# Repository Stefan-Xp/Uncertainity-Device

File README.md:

# Uncertainity-Device
Uncertainity Device - A small PCB with ESP32s2 and WS2812 compatible LEDs

Attention: This Design is not yet tested, so proceed with caution!

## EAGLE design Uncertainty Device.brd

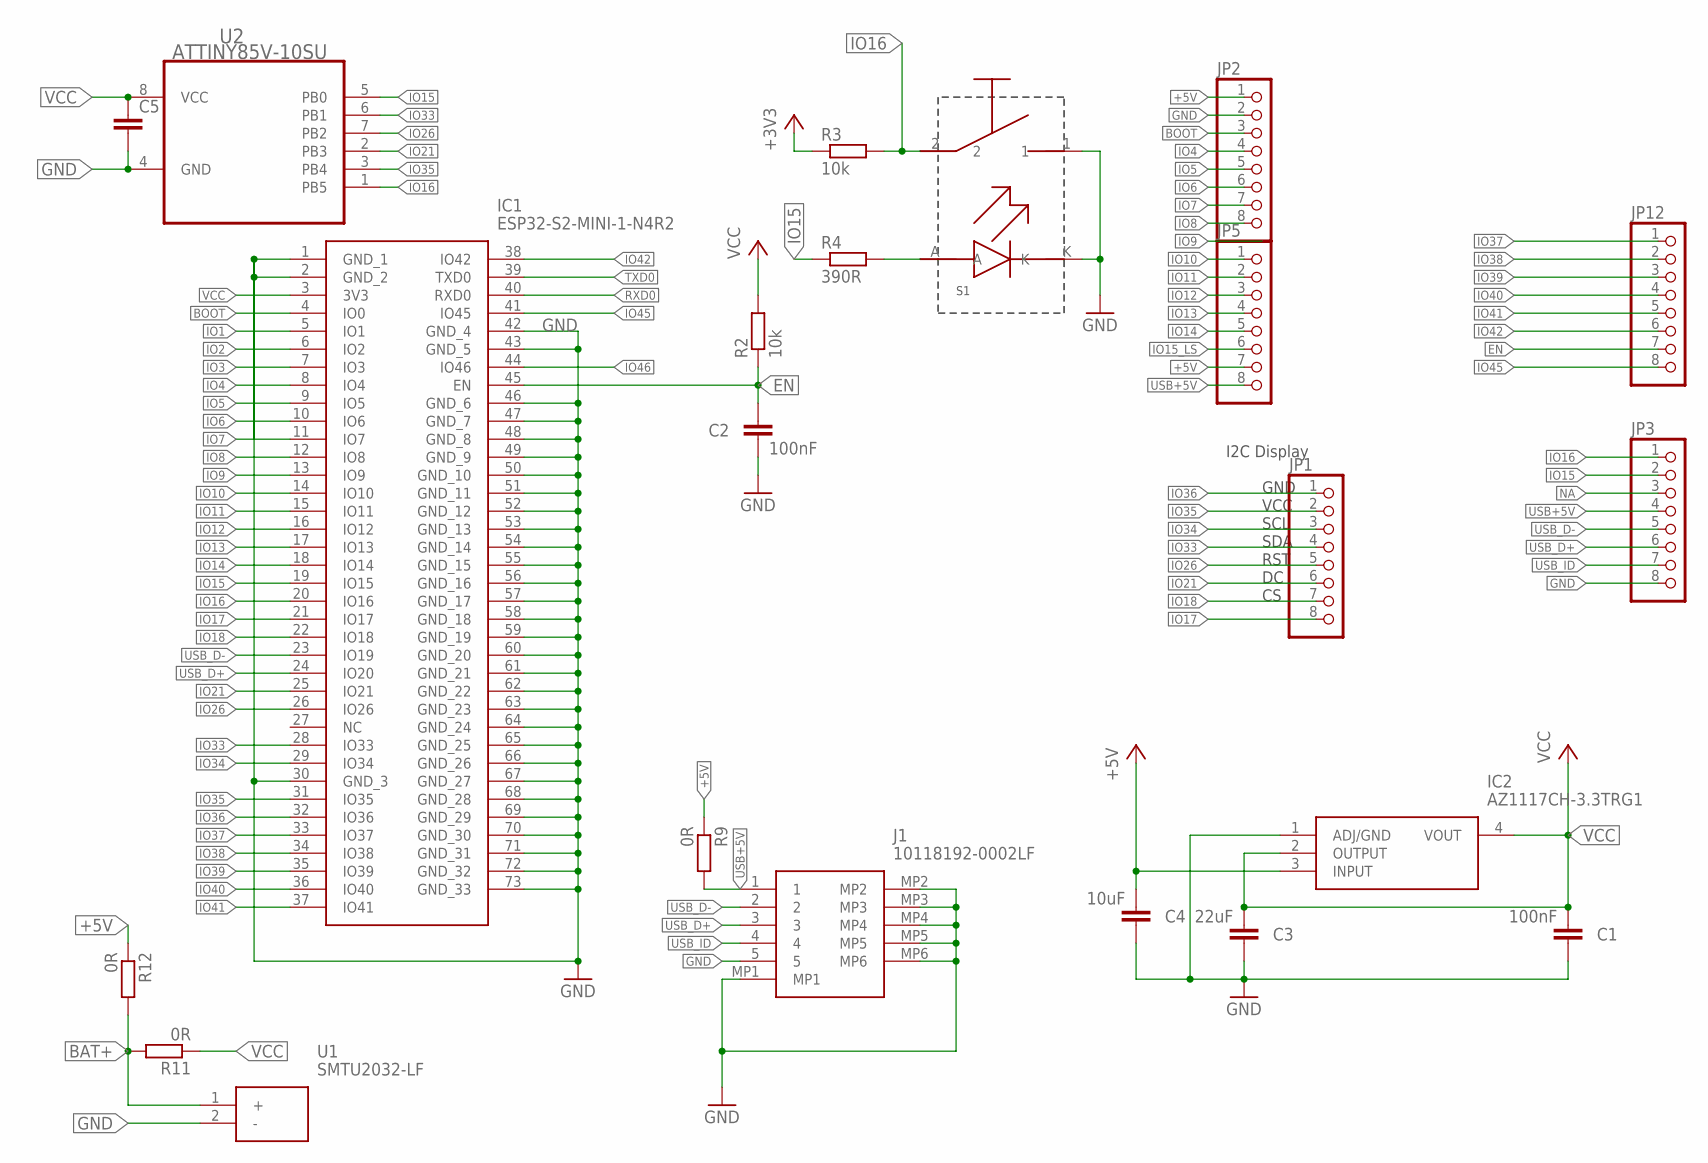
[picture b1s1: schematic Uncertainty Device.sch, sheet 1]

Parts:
C1, C2: 100nF; C0805
C3: 22uF; C0805
C4: 10uF; C0805
C5: C-EUC0805; C0805
IC1: ESP32-S2-MINI-1-N4R2; ESP32S2MINI1N4R2
IC2: AZ1117CH-3.3TRG1; SOT230P700X180-4N
J1: 10118192-0002LF; 101181920002LF
JP1, JP2, JP3, JP5, JP12: PINHD-1X8; 1X08
R2, R3: 10k; R0805
R4: 390R; R0805
R9, R11, R12: 0R; R0805
S1: 3006SMD; SMD
U1: SMTU2032-LF; SMTU2032LF
U2: ATTINY85V-10SU; SOIC127P798X216-8N

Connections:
+3V3: R3.1
+5V: C4.2, IC2.3 (INPUT), JP2.1, JP5.7, R9.1, R12.1
BAT+: R11.2, R12.2, U1.1 (+)
BOOT: IC1.4 (IO0), JP2.3
EN: C2.1, IC1.45 (EN), JP12.7, R2.1
GND: C1.1, C2.2, C3.1, C4.1, C5.2, IC1.1 (GND_1), IC1.2 (GND_2), IC1.30 (GND_3), IC1.42 (GND_4), IC1.43 (GND_5), IC1.46 (GND_6), IC1.47 (GND_7), IC1.48 (GND_8), IC1.49 (GND_9), IC1.50 (GND_10), IC1.51 (GND_11), IC1.52 (GND_12), IC1.53 (GND_13), IC1.54 (GND_14), IC1.55 (GND_15), IC1.56 (GND_16), IC1.57 (GND_17), IC1.58 (GND_18), IC1.59 (GND_19), IC1.60 (GND_20), IC1.61 (GND_21), IC1.62 (GND_22), IC1.63 (GND_23), IC1.64 (GND_24), IC1.65 (GND_25), IC1.66 (GND_26), IC1.67 (GND_27), IC1.68 (GND_28), IC1.69 (GND_29), IC1.70 (GND_30), IC1.71 (GND_31), IC1.72 (GND_32), IC1.73 (GND_33), IC2.1 (ADJ/GND), J1.5, J1.MP1, J1.MP2, J1.MP3, J1.MP4, J1.MP5, J1.MP6, JP2.2, JP3.8, S1.1, S1.K, U1.2 (-), U2.4 (GND); also elsewhere on the board
IO1: IC1.5 (IO1)
IO2: IC1.6 (IO2)
IO3: IC1.7 (IO3)
IO4: IC1.8 (IO4), JP2.4
IO5: IC1.9 (IO5), JP2.5
IO6: IC1.10 (IO6), JP2.6
IO7: IC1.11 (IO7), JP2.7
IO8: IC1.12 (IO8), JP2.8
IO9: IC1.13 (IO9)
IO10: IC1.14 (IO10), JP5.1
IO11: IC1.15 (IO11), JP5.2
IO12: IC1.16 (IO12), JP5.3
IO13: IC1.17 (IO13), JP5.4
IO14: IC1.18 (IO14), JP5.5
IO15: IC1.19 (IO15), JP3.2, R4.1, U2.5 (PB0)
IO15_LS: JP5.6
IO16: IC1.20 (IO16), JP3.1, R3.2, S1.2, U2.1 (PB5)
IO17: IC1.21 (IO17), JP1.8; also elsewhere on the board
IO18: IC1.22 (IO18), JP1.7; also elsewhere on the board
IO21: IC1.25 (IO21), JP1.6, U2.2 (PB3); also elsewhere on the board
IO26: IC1.26 (IO26), JP1.5, U2.7 (PB2); also elsewhere on the board
IO33: IC1.28 (IO33), JP1.4, U2.6 (PB1); also elsewhere on the board
IO34: IC1.29 (IO34), JP1.3; also elsewhere on the board
IO35: IC1.31 (IO35), JP1.2, U2.3 (PB4); also elsewhere on the board
IO36: IC1.32 (IO36), JP1.1
IO37: IC1.33 (IO37), JP12.1
IO38: IC1.34 (IO38), JP12.2
IO39: IC1.35 (IO39), JP12.3
IO40: IC1.36 (IO40), JP12.4
IO41: IC1.37 (IO41), JP12.5
IO42: IC1.38 (IO42), JP12.6
IO45: IC1.41 (IO45), JP12.8
IO46: IC1.44 (IO46)
unnamed: R4.2, S1.A
NA: JP3.3
RXD0: IC1.40 (RXD0)
TXD0: IC1.39 (TXD0)
USB+5V: J1.1, JP3.4, JP5.8, R9.2
USB_D+: IC1.24 (IO20), J1.3, JP3.6
USB_D-: IC1.23 (IO19), J1.2, JP3.5
USB_ID: J1.4, JP3.7
VCC: C1.2, C3.2, C5.1, IC1.3 (3V3), IC2.2 (OUTPUT), IC2.4 (VOUT), R2.2, R11.1, U2.8 (VCC)

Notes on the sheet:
GND
VCC
SCL
SDA
RST
I2C Display

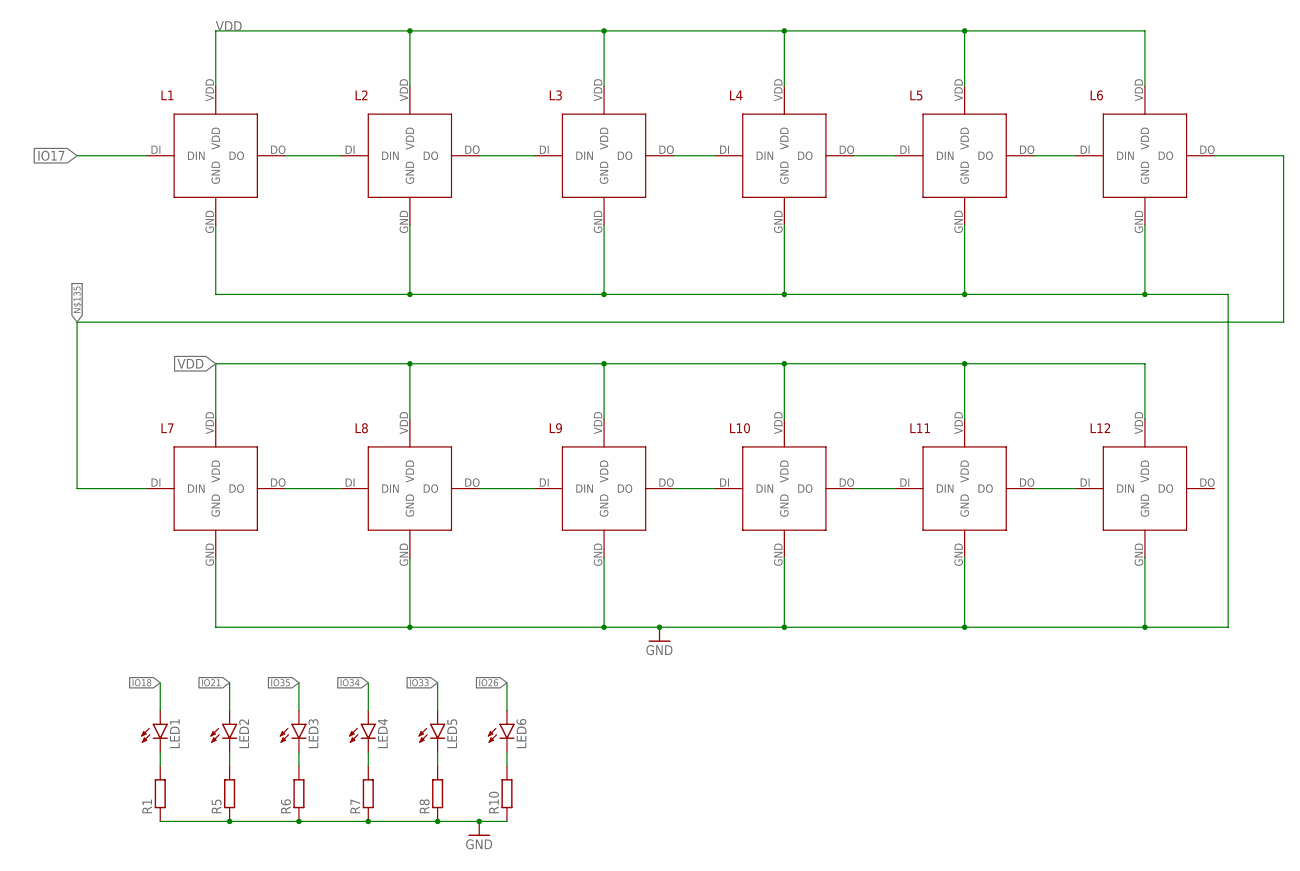
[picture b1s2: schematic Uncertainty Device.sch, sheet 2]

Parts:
L1, L2, L3, L4, L5, L6, L7, L8, L9, L10, L11, L12: XL-1615RGBC; XL-1615RGBC-WS2812
LED1, LED2, LED3, LED4, LED5, LED6: LEDCHIPLED_0805; CHIPLED_0805
R1, R5, R6, R7, R8, R10: R-EU_R0805; R0805

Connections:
GND: L1.GND, L2.GND, L3.GND, L4.GND, L5.GND, L6.GND, L7.GND, L8.GND, L9.GND, L10.GND, L11.GND, L12.GND, R1.1, R5.1, R6.1, R7.1, R8.1, R10.1; also elsewhere on the board
IO17: L1.DI (DIN); also elsewhere on the board
IO18: LED1.A; also elsewhere on the board
IO21: LED2.A; also elsewhere on the board
IO26: LED6.A; also elsewhere on the board
IO33: LED5.A; also elsewhere on the board
IO34: LED4.A; also elsewhere on the board
IO35: LED3.A; also elsewhere on the board
unnamed: LED1.C, R1.2
unnamed: L1.DO, L2.DI (DIN)
unnamed: L2.DO, L3.DI (DIN)
unnamed: L3.DO, L4.DI (DIN)
unnamed: L4.DO, L5.DI (DIN)
unnamed: L5.DO, L6.DI (DIN)
unnamed: L7.DO, L8.DI (DIN)
unnamed: L8.DO, L9.DI (DIN)
unnamed: L9.DO, L10.DI (DIN)
unnamed: L10.DO, L11.DI (DIN)
unnamed: L11.DO, L12.DI (DIN)
unnamed: LED2.C, R5.2
unnamed: LED3.C, R6.2
unnamed: LED4.C, R7.2
unnamed: LED5.C, R8.2
unnamed: LED6.C, R10.2
unnamed: L6.DO, L7.DI (DIN)
VDD: L1.VDD, L2.VDD, L3.VDD, L4.VDD, L5.VDD, L6.VDD, L7.VDD, L8.VDD, L9.VDD, L10.VDD, L11.VDD, L12.VDD

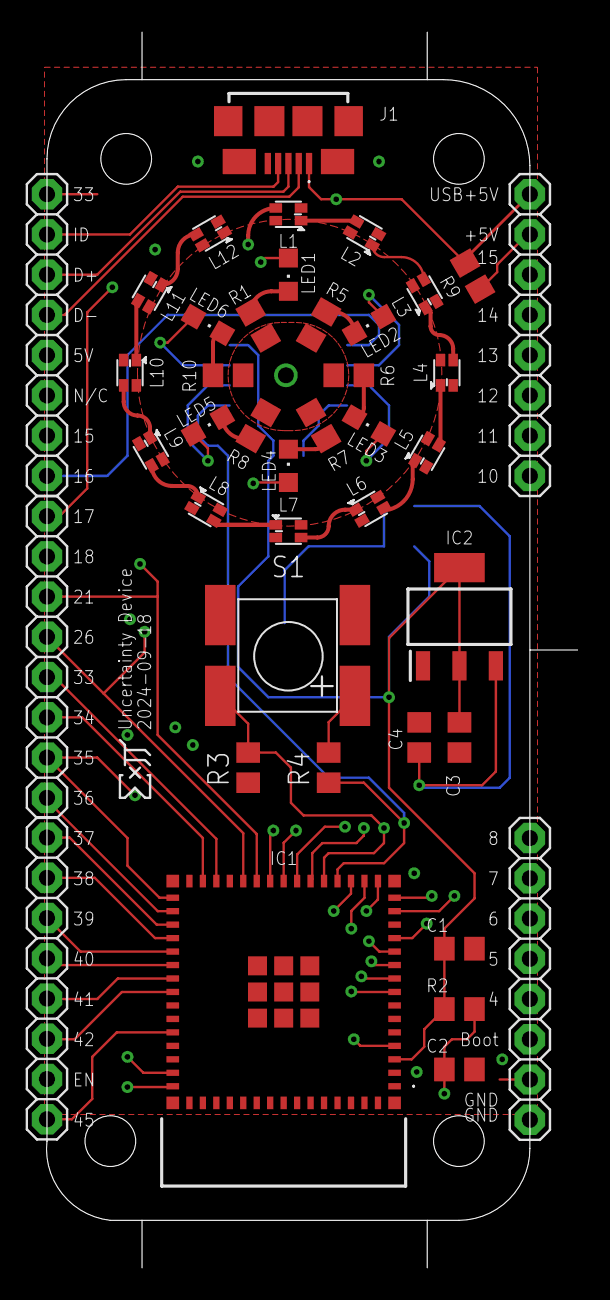
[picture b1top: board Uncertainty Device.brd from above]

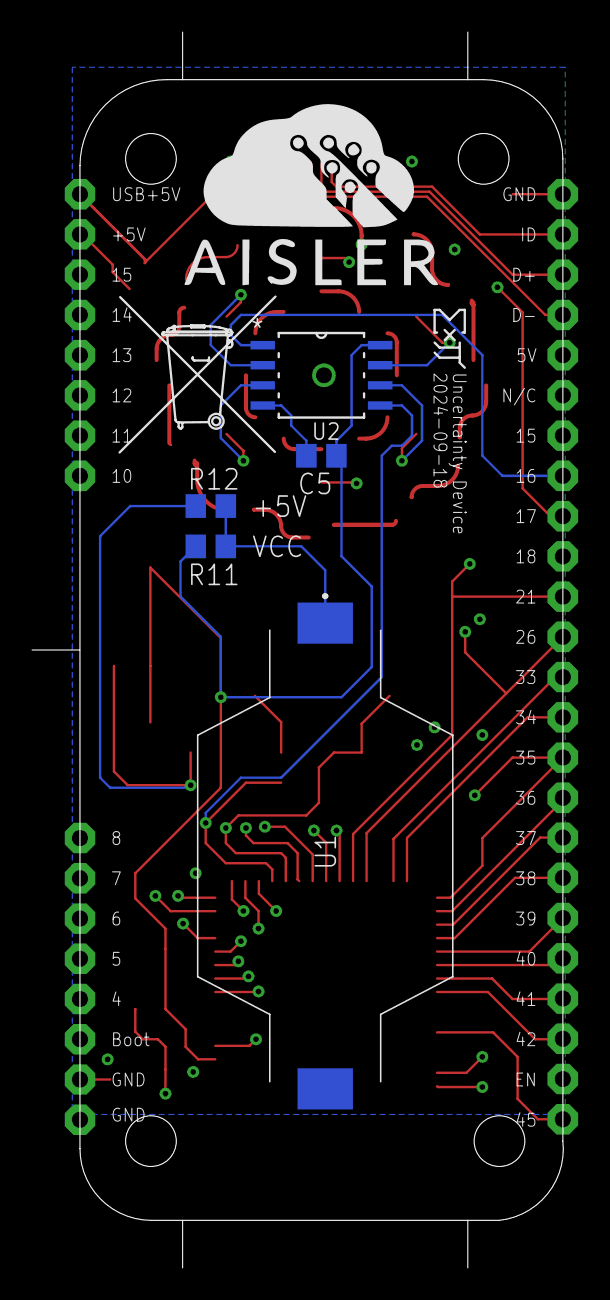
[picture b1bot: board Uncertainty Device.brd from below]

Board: 4 copper layers, 33.5 x 78.0 mm, 48 parts (7 on the bottom side), 56 nets.

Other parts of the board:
U$1: AISLER
U$3: TONNE_10.00

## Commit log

2024-10-20 Added Upload to Aisler button
2024-10-20 Fixed Link
2024-10-20 Update README.md
    Added Warning
2024-10-20 Added Pictures of the Design
2024-10-20 Added PCB Design Pictures
